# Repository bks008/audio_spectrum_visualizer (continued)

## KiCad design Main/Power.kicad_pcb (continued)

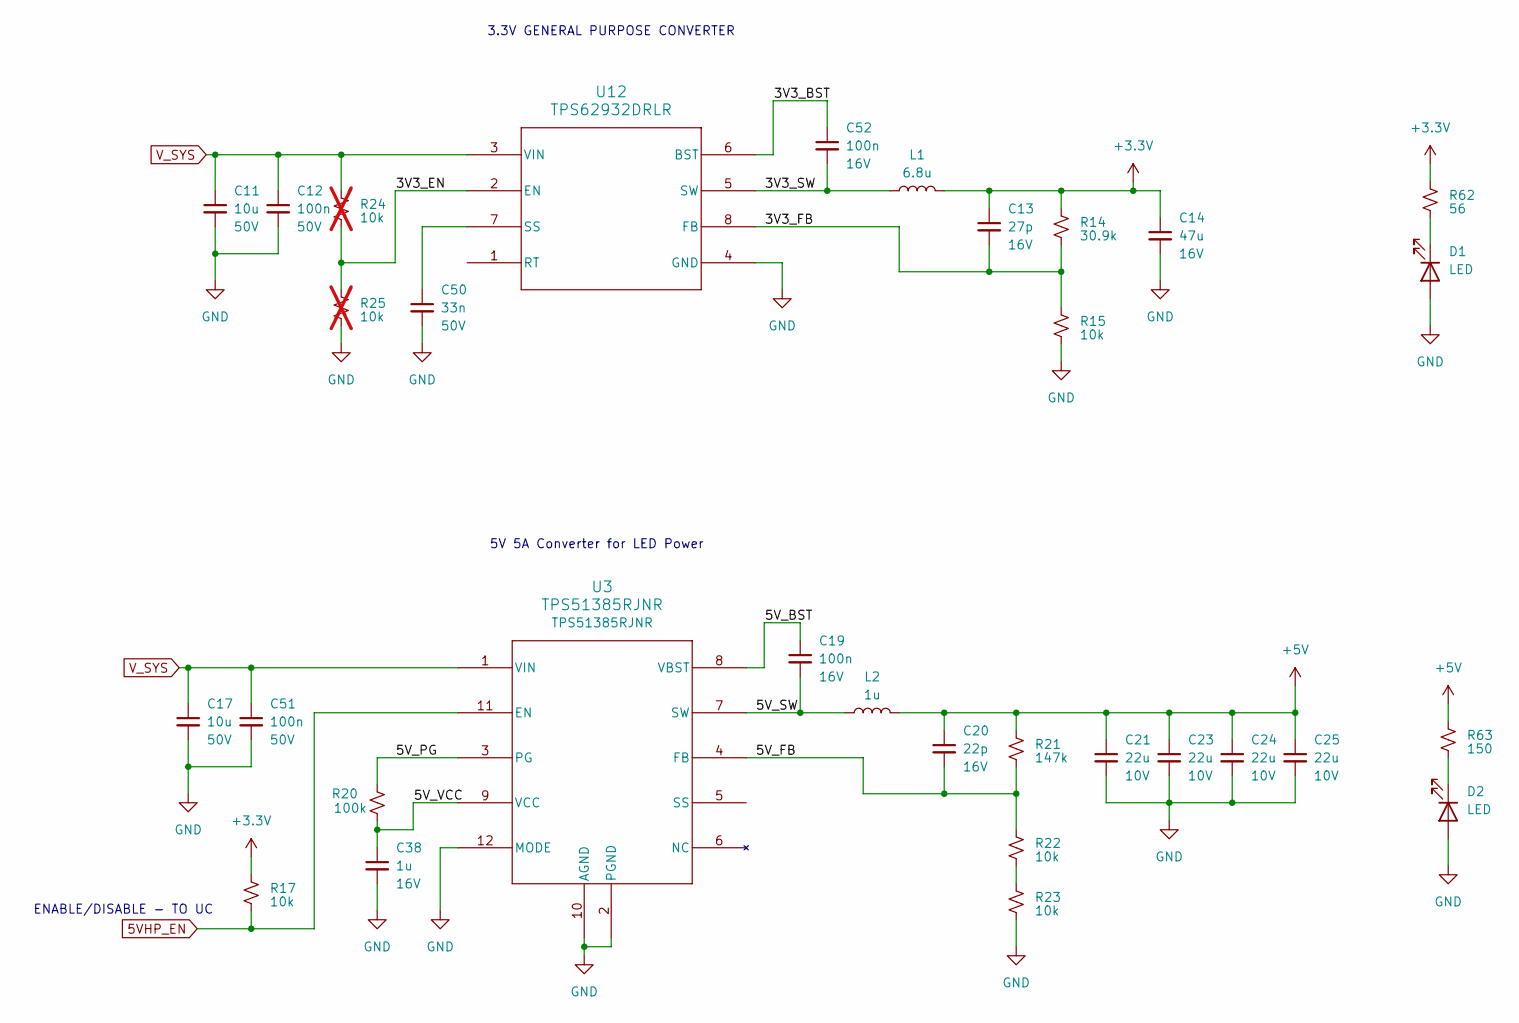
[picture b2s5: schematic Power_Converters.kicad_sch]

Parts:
C11, C17: 10u; C_1206_3216Metric_Pad1.33x1.80mm_HandSolder; Voltage 50V; Part Number C3216X5R1H106K160AB
C12, C51: 100n; C_0805_2012Metric_Pad1.18x1.45mm_HandSolder; Voltage 50V; Part Number GRM21BR71H104KA01L
C13: 27p; C_0805_2012Metric_Pad1.18x1.45mm_HandSolder; Voltage 16V; Part Number 0805YA270JAT2A
C14: 47u; C_1210_3225Metric_Pad1.33x2.70mm_HandSolder; Voltage 16V; Part Number GRM32ER61C476KE15L
C19, C52: 100n; C_0805_2012Metric_Pad1.18x1.45mm_HandSolder; Voltage 16V; Part Number 0805YC104MAT2A
C20: 22p; C_0805_2012Metric_Pad1.18x1.45mm_HandSolder; Voltage 16V; Part Number 0805YA220JAT2A
C21, C23, C24, C25: 22u; C_1206_3216Metric_Pad1.33x1.80mm_HandSolder; Voltage 10V; Part Number GRM31CR71A226KE15L
C38: 1u; C_0805_2012Metric_Pad1.18x1.45mm_HandSolder; Voltage 16V; Part Number GCJ21BR71C105KA01L
C50: 33n; C_0805_2012Metric_Pad1.18x1.45mm_HandSolder; Voltage 50V; Part Number GRM21BR71H104KA01L
D1, D2: LED; LED_0805_2012Metric_Pad1.15x1.40mm_HandSolder; Part Number APT2012PGW
L1: 6.8u; L_Coilcraft_XAL7070-XXX; Part Number XAL7070-682MEB
L2: 1u; L_Coilcraft_XAL6030-XXX; Part Number XAL6030-102MEB
R14: 30.9k; R_0805_2012Metric_HandSolder; Part Number CRCW080530K9FKEA
R15, R17, R22, R23: 10k; R_0805_2012Metric_HandSolder; Part Number CRCW080510K0FKEA
R20: 100k; R_0805_2012Metric_HandSolder; Part Number CRCW0805100KFKEA
R21: 147k; R_0805_2012Metric_HandSolder; Part Number CRCW0805147KFKEA
R24, R25: 10k; R_0805_2012Metric_HandSolder; Part Number CRCW080510K0FKEA; not fitted
R62: 56; R_0805_2012Metric_HandSolder; Part Number CRCW080556R0FKEA
R63: 150; R_0805_2012Metric_HandSolder; Part Number CRCW0805150RFKEA
U3: TPS51385RJNR; VQFN-HR12_RJN_TEX; Part Number TPS51385RJNR
U12: TPS62932DRLR; SOT8_DRL_TEX; Part Number TPS62932DRLR

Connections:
5VHP_EN: R17.2, U3.11 (EN); also elsewhere on the board
+3.3V: C13.1, C14.1, L1.2, R14.1, R17.1, R62.1; also elsewhere on the board
+5V: C20.1, C21.1, C23.1, C24.1, C25.1, L2.2, R21.1, R63.1; also elsewhere on the board
/Power_Converters/3V3_BST: C52.1, U12.6 (BST)
/Power_Converters/3V3_EN: R24.2, R25.1, U12.2 (EN)
/Power_Converters/3V3_FB: C13.2, R14.2, R15.1, U12.8 (FB)
/Power_Converters/3V3_SW: C52.2, L1.1, U12.5 (SW)
/Power_Converters/5V_BST: C19.1, U3.8 (VBST)
/Power_Converters/5V_FB: C20.2, R21.2, R22.1, U3.4 (FB)
/Power_Converters/5V_PG: R20.1, U3.3 (PG)
/Power_Converters/5V_SW: C19.2, L2.1, U3.7 (SW)
/Power_Converters/5V_VCC: C38.1, R20.2, U3.9 (VCC)
GND: C11.2, C12.2, C14.2, C17.2, C21.2, C23.2, C24.2, C25.2, C38.2, C50.2, C51.2, D1.2 (A), D2.2 (A), R15.2, R23.2, R25.2, U3.2 (PGND), U3.10 (AGND), U3.12 (MODE), U12.4 (GND); also elsewhere on the board
unnamed: D1.1 (K), R62.2
unnamed: D2.1 (K), R63.2
unnamed: R22.2, R23.1
unnamed: C50.1, U12.7 (SS)
V_SYS: C11.1, C12.1, C17.1, C51.1, R24.1, U3.1 (VIN), U12.3 (VIN); also elsewhere on the board

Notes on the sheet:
5V 5A Converter for LED Power
ENABLE/DISABLE - TO UC
3.3V GENERAL PURPOSE CONVERTER

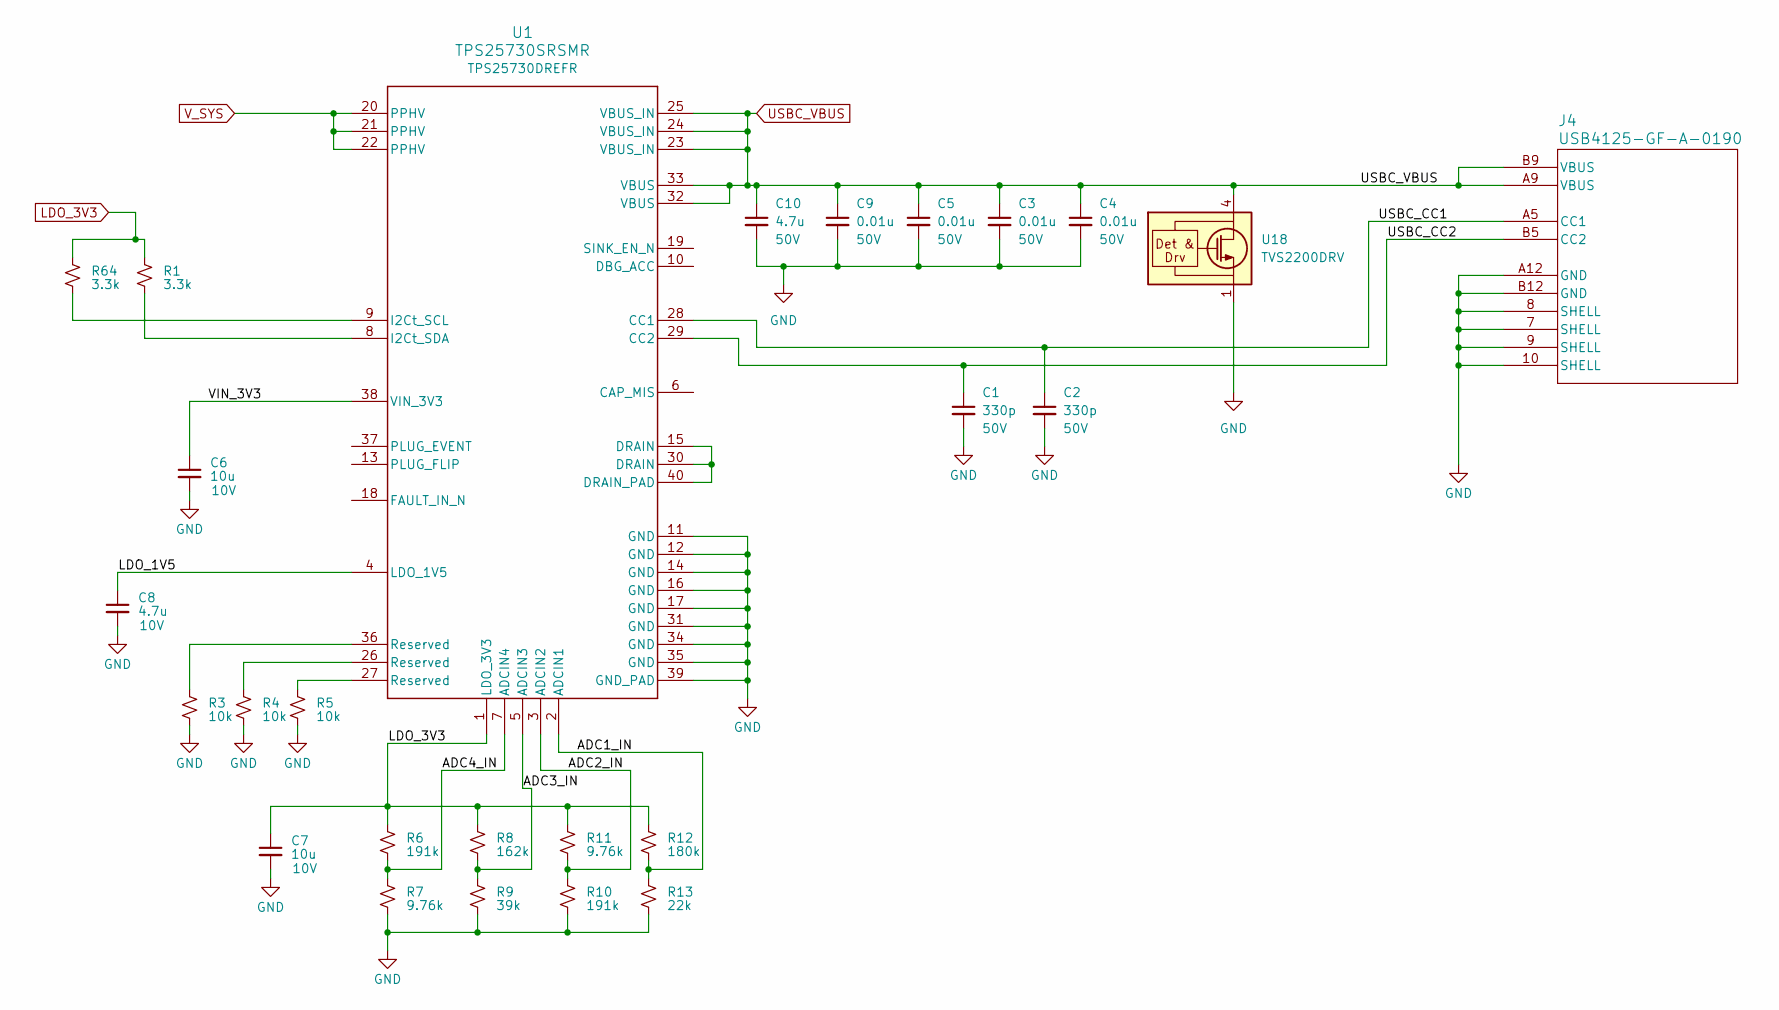
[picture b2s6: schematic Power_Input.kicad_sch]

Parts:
C1, C2: 330p; C_0805_2012Metric_Pad1.18x1.45mm_HandSolder; Voltage 50V; Part Number 08055A331GAT2A
C3, C4, C5, C9: 0.01u; C_0805_2012Metric_Pad1.18x1.45mm_HandSolder; Voltage 50V; Part Number 08055C103ZAT2A
C6, C7: 10u; C_0805_2012Metric_Pad1.18x1.45mm_HandSolder; Voltage 10V; Part Number MBASL21GBB7106KTNA18
C8: 4.7u; C_0805_2012Metric_Pad1.18x1.45mm_HandSolder; Voltage 10V; Part Number GRM219R61A475KE32D
C10: 4.7u; C_0805_2012Metric_Pad1.18x1.45mm_HandSolder; Voltage 50V; Part Number GRM21BC71H475KE11K
J4: USB4125-GF-A-0190; CONN6_125-GF-A-0190_GCT; Part Number USB4125-GF-A-0190
R1, R64: 3.3k; R_0805_2012Metric_Pad1.20x1.40mm_HandSolder; Part Number CRCW08053K30FKEA
R3, R4, R5: 10k; R_0805_2012Metric_HandSolder; Part Number CRCW080510K0FKEA
R6, R10: 191k; R_0805_2012Metric_HandSolder; Part Number CRCW0805191KFKEA
R7, R11: 9.76k; R_0805_2012Metric_HandSolder; Part Number CRCW08059K76FKEA
R8: 162k; R_0805_2012Metric_HandSolder; Part Number CRCW0805162KFKEA
R9: 39k; R_0805_2012Metric_HandSolder; Part Number CRCW080539K0FKEA
R12: 180k; R_0805_2012Metric_HandSolder; Part Number CRCW0805180KFKEA
R13: 22k; R_0805_2012Metric_HandSolder; Part Number CRCW080522K0FKEA
U1: TPS25730SRSMR; REF0038A-MFG; Part Number TPS25730DREFR
U18: TVS2200DRV; WSON-6-1EP_2x2mm_P0.65mm_EP1x1.6mm; Part Number TVS2200DRV

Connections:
/Power_Input/ADC1_IN: R12.2, R13.1, U1.2 (ADCIN1)
/Power_Input/ADC2_IN: R10.1, R11.2, U1.3 (ADCIN2)
/Power_Input/ADC3_IN: R8.2, R9.1, U1.5 (ADCIN3)
/Power_Input/ADC4_IN: R6.2, R7.1, U1.7 (ADCIN4)
/Power_Input/LDO_1V5: C8.1, U1.4 (LDO_1V5)
/Power_Input/USBC_CC1: C2.1, J4.A5 (CC1), U1.28 (CC1)
/Power_Input/USBC_CC2: C1.1, J4.B5 (CC2), U1.29 (CC2)
/Power_Input/VIN_3V3: C6.1, U1.38 (VIN_3V3)
GND: C1.2, C2.2, C3.2, C4.2, C5.2, C6.2, C7.2, C8.2, C9.2, C10.2, J4.7 (SHELL), J4.8 (SHELL), J4.9 (SHELL), J4.10 (SHELL), J4.A12 (GND), J4.B12 (GND), R3.2, R4.2, R5.2, R7.2, R9.2, R10.2, R13.2, U1.11 (GND), U1.12 (GND), U1.14 (GND), U1.16 (GND), U1.17 (GND), U1.31 (GND), U1.34 (GND), U1.35 (GND), U1.39 (GND_PAD), U18.1 (GND), U18.2 (GND), U18.3 (GND), U18.7 (GND); also elsewhere on the board
LDO_3V3: C7.1, R1.1, R6.1, R8.1, R11.1, R12.1, R64.1, U1.1 (LDO_3V3)
unnamed: R3.1, U1.36 (Reserved)
unnamed: R4.1, U1.26 (Reserved)
unnamed: R5.1, U1.27 (Reserved)
unnamed: U1.15 (DRAIN), U1.30 (DRAIN), U1.40 (DRAIN_PAD)
unnamed: R64.2, U1.9 (I2Ct_SCL)
unnamed: R1.2, U1.8 (I2Ct_SDA)
USBC_VBUS: C3.1, C4.1, C5.1, C9.1, C10.1, J4.A9 (VBUS), J4.B9 (VBUS), U1.23 (VBUS_IN), U1.24 (VBUS_IN), U1.25 (VBUS_IN), U1.32 (VBUS), U1.33 (VBUS), U18.4 (IN), U18.5 (IN), U18.6 (IN)
V_SYS: U1.20 (PPHV), U1.21 (PPHV), U1.22 (PPHV); also elsewhere on the board

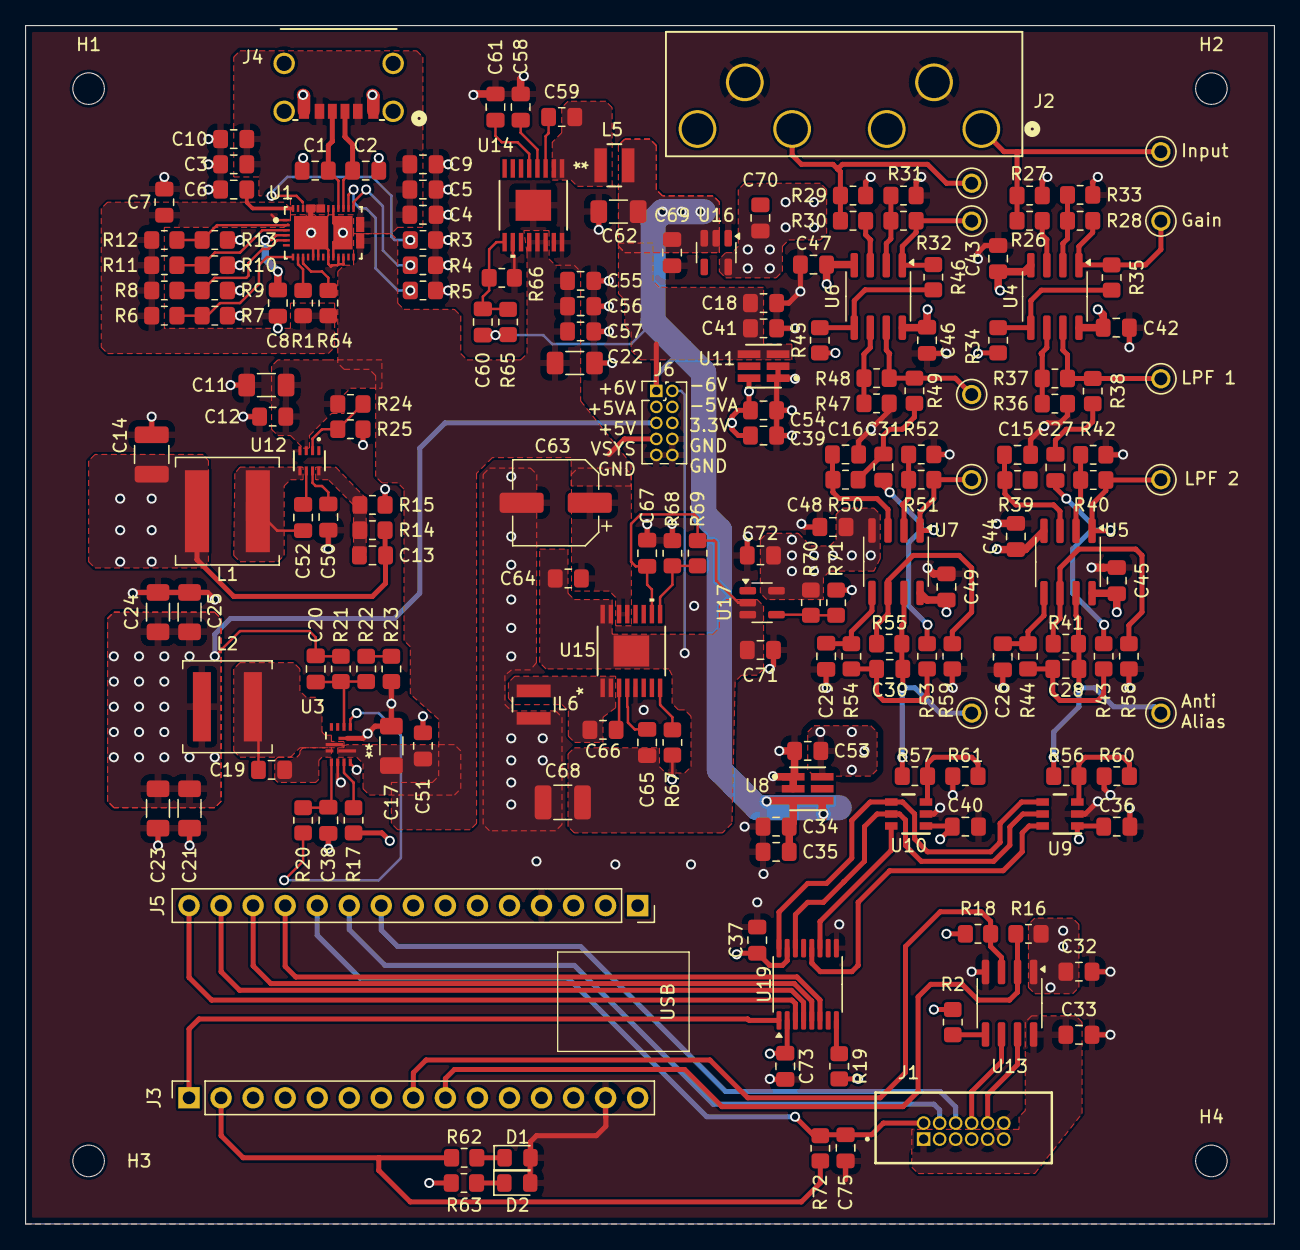
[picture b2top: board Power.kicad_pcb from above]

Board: 4 copper layers, 99.0 x 95.0 mm, 190 parts (1 on the bottom side), 100 nets.

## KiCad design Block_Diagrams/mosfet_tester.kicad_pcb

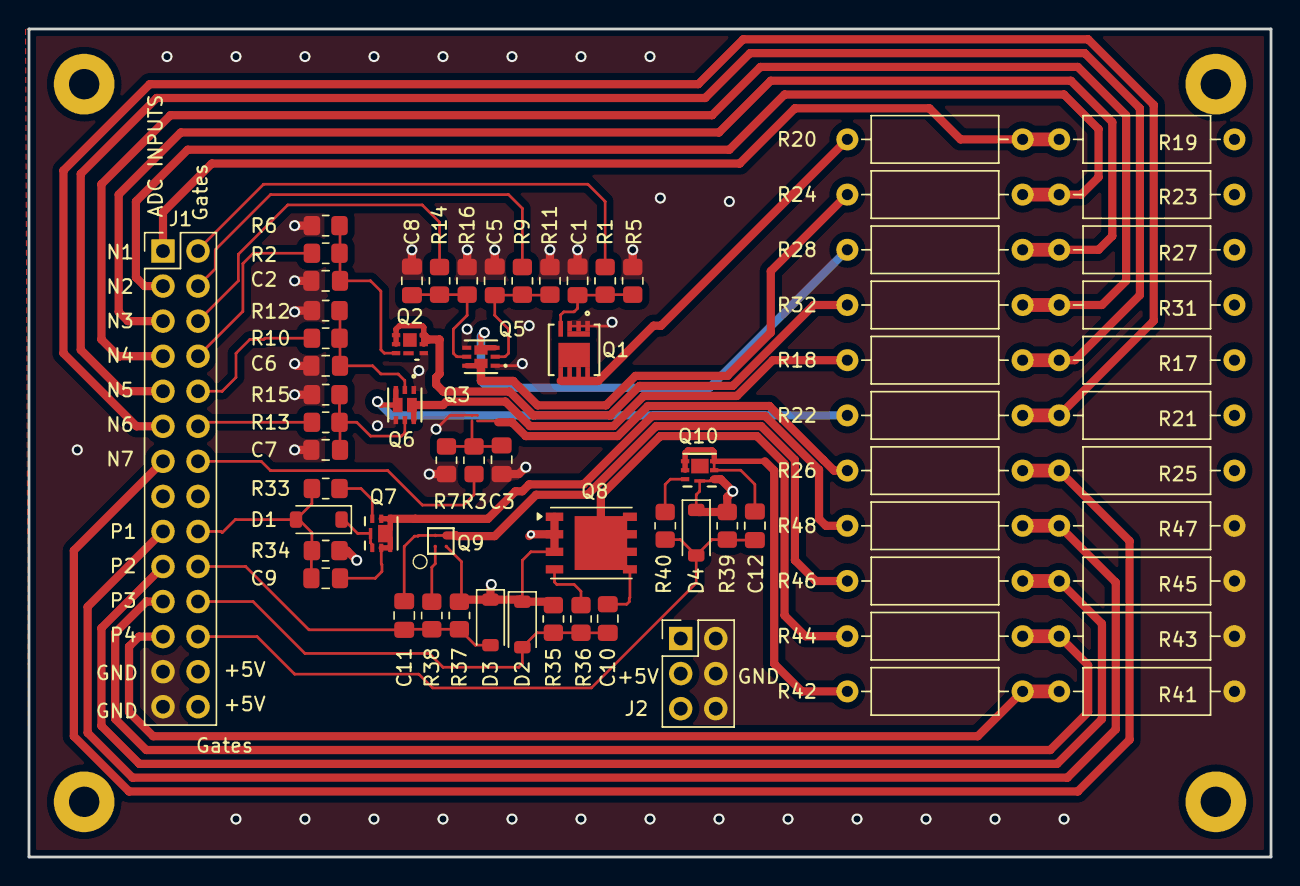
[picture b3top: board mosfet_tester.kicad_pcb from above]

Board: 2 copper layers, 90.0 x 60.0 mm, 70 parts (0 on the bottom side), 46 nets.

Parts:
C1, C2, C3, C5, C6, C7, C8, C9, C10, C11, C12: 1000p; C_0805_2012Metric_Pad1.18x1.45mm_HandSolder
D1, D2, D3, D4: MMSZ5238BT1G; D_SOD-123
J1: Conn_02x14_Odd_Even; PinHeader_2x14_P2.54mm_Vertical
J2: Conn_02x03_Odd_Even; PinHeader_2x03_P2.54mm_Vertical
Q1: IPZ40N04S5L7R4ATMA1; PG-TSDSON-8-32_INF
Q2: CSD17318Q2T; DQK6_TEX
Q3: SI8812DB-T2-E1; MICROFOOT4_0P8X0P8-0P4_VIS
Q5: IRLHS6376TRPBF; PQFN6_IRLHS6376TRPBF_INF
Q6: SIA918EDJ-T1-GE3; SON_EDJ-T1-GE3_VIS
Q7: IRLHS2242TRPBF; PQFN6_2X2_INF
Q8: SI7489DP-T1-GE3; PowerPAK_SO-8_Single
Q9: SI8409DB-T1-E1; MICROFOOT4_1p6X1p6-0p8_VIS
Q10: SQA413CEJW-T1_GE3; PQFN6_2X2_INF
R1, R2, R3, R9, R10, R13, R14, R33, R36, R38, R40: 47; R_0805_2012Metric_HandSolder
R5, R6, R7, R11, R12, R15, R16, R34, R35, R37, R39: 10K; R_0805_2012Metric_HandSolder
R17, R18, R19, R20, R21, R22, R23, R24, R25, R26, R27, R28, R31, R32, R41, R42, R43, R44, R45, R46, R47, R48: 10; R_Axial_DIN0309_L9.0mm_D3.2mm_P12.70mm_Horizontal

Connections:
+5V: D1.1 (K), D2.1 (K), D3.1 (K), D4.1 (K), J1.26, J1.28, J2.1, J2.3, J2.5, Q7.4 (S), Q7.8 (S), Q8.1 (S), Q8.2 (S), Q8.3 (S), Q9.4 (S), Q10.4 (S), Q10.7 (S), R17.1, R19.1, R21.1, R23.1, R25.1, R27.1, R31.1, R34.1, R35.1, R37.1, R39.1
GND: C1.2, C2.2, C3.2, C5.2, C6.2, C7.2, C8.2, J1.25, J1.27, J2.2, J2.4, J2.6, Q1.1 (S), Q1.2 (S), Q1.3 (S), Q2.4 (S), Q3.2 (S), Q3.3 (S), Q5.1 (S1), Q5.4 (S2), Q6.1 (S1), Q6.4 (S2), R5.2, R6.2, R7.2, R11.2, R12.2, R15.2, R16.2, R41.2, R43.2, R45.2, R47.2
N1_GATE: J1.2, R1.1
N1_LOAD: Q1.5 (D), Q1.6 (D), Q1.7 (D), Q1.8 (D), R20.2
N2_GATE: J1.4, R9.1
N2_LOAD: Q5.6 (D1), Q5.7 (D1), R24.2
N3_GATE: J1.6, R14.1
N3_LOAD: Q5.3 (D2), Q5.8 (D2), R28.2
N4_GATE: J1.8, R2.1
N4_LOAD: Q2.1 (D), Q2.2 (D), Q2.5 (D), Q2.6 (D), R32.2
N5_GATE: J1.10, R10.1
N5_LOAD: Q6.6 (D1), Q6.7 (D1), R18.2
N6_GATE: J1.12, R13.1
N6_LOAD: Q6.3 (D2), Q6.8 (D2), R22.2
N7_GATE: J1.14, R3.1
N7_LOAD: Q3.4 (D), R26.2
unnamed: J1.1, R19.2, R20.1
unnamed: J1.3, R23.2, R24.1
unnamed: J1.5, R27.2, R28.1
unnamed: J1.7, R31.2, R32.1
unnamed: J1.9, R17.2, R18.1
unnamed: J1.11, R21.2, R22.1
unnamed: J1.13, R25.2, R26.1
unnamed: J1.17, R47.1, R48.1
unnamed: J1.19, R45.1, R46.1
unnamed: J1.21, R43.1, R44.1
unnamed: J1.23, R41.1, R42.1
unnamed: C1.1, Q1.4 (G), R1.2, R5.1
unnamed: C2.1, Q2.3 (G), R2.2, R6.1
unnamed: C3.1, Q3.1 (G), R3.2, R7.1
unnamed: C5.1, Q5.2 (G1), R9.2, R11.1
unnamed: C8.1, Q5.5 (G2), R14.2, R16.1
unnamed: C6.1, Q6.2 (G1), R10.2, R12.1
unnamed: C7.1, Q6.5 (G2), R13.2, R15.1
unnamed: Q7.3 (G), R33.2
unnamed: Q8.4 (G), R36.2
unnamed: Q9.1 (G), R38.2
unnamed: Q10.3 (G), R40.2
P1_GATE: C9.2, D1.2 (A), J1.18, R33.1, R34.2
P1_LOAD: C9.1, Q7.1 (D), Q7.2 (D), Q7.5 (D), Q7.6 (D), Q7.7 (D), R48.2
P2_GATE: C11.2, D3.2 (A), J1.20, R37.2, R38.1
P2_LOAD: C11.1, Q9.2 (D), Q9.3 (D), R46.2
P3_GATE: C10.2, D2.2 (A), J1.22, R35.2, R36.1
P3_LOAD: C10.1, Q8.5 (D), R44.2
P4_GATE: C12.2, D4.2 (A), J1.24, R39.2, R40.1
P4_LOAD: C12.1, Q10.1 (D), Q10.2 (D), Q10.5 (D), Q10.6 (D), R42.2
